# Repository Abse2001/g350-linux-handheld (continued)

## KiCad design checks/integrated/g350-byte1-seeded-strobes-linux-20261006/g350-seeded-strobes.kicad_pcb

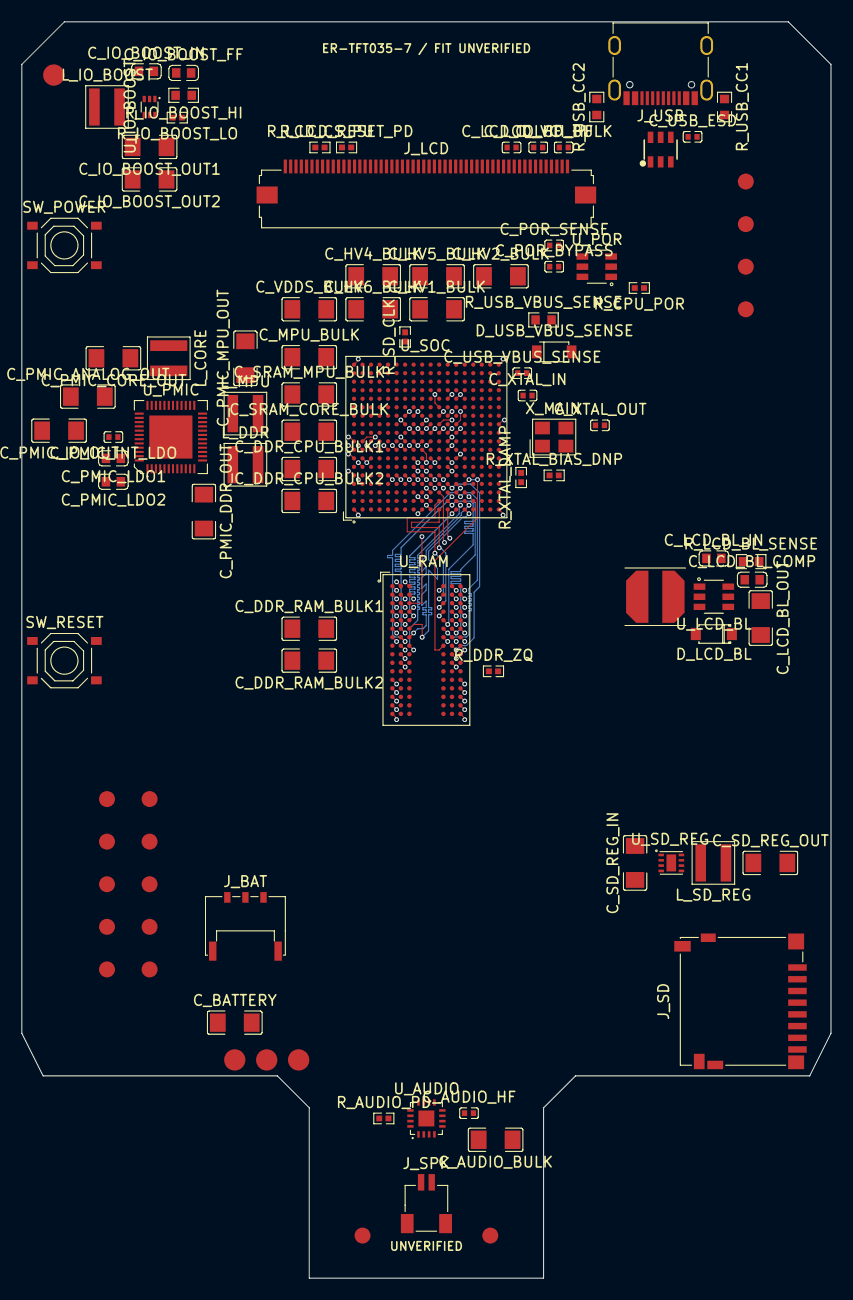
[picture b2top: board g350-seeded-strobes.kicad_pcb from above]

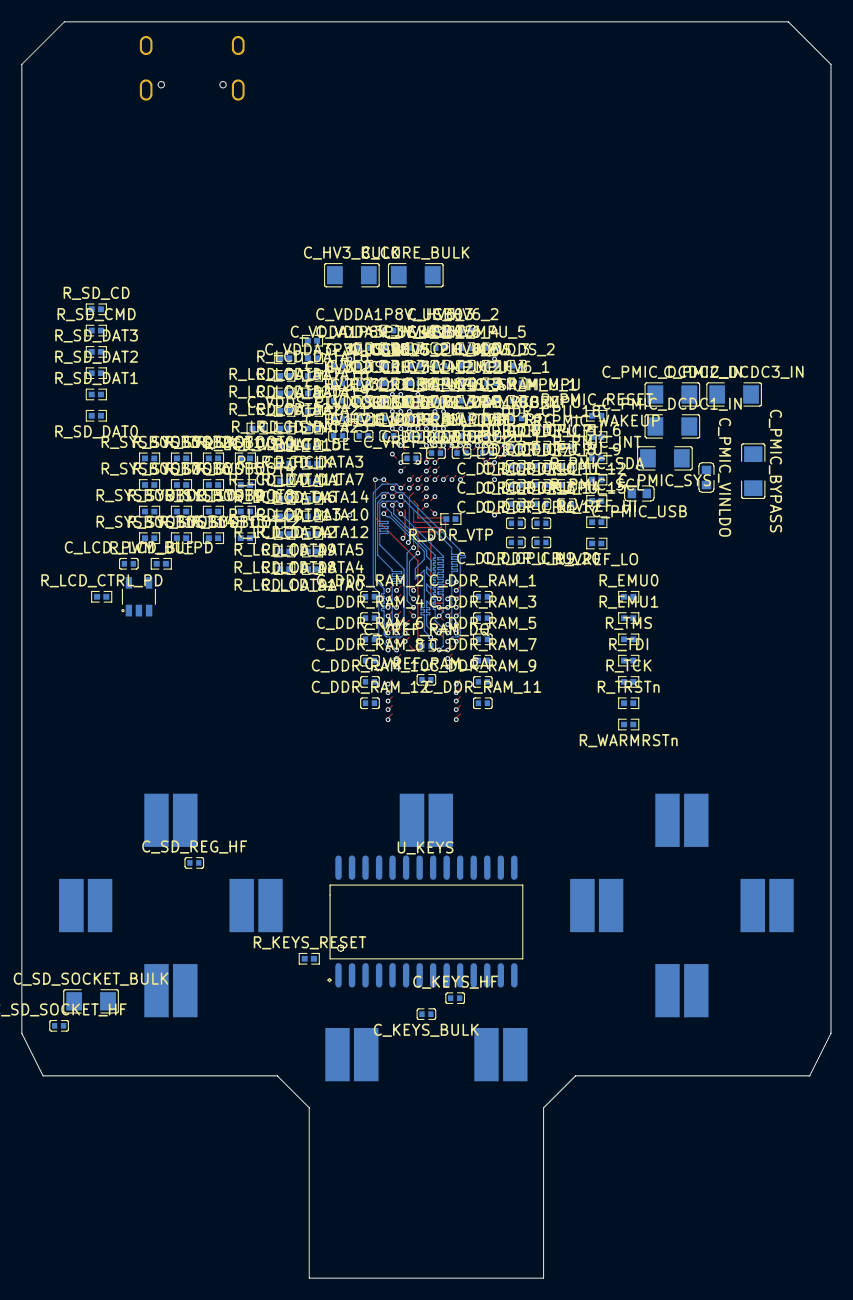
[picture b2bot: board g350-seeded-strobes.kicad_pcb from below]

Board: 4 copper layers, 76.0 x 118.0 mm, 280 parts (179 on the bottom side), 198 nets.

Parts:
C_AUDIO_BULK: 22uF; g350_C_AUDIO_BULK_392600202ec82a7f246a54de1a0c7f3d
C_AUDIO_HF: 100nF; g350_C_AUDIO_HF_6961d4c073bfaa617e1d80027784aa5d
C_BATTERY: 22uF; g350_C_BATTERY_017ffda058f040414c9f81de0dd0bc03
C_CAP_VBB_MPU: 1uF; g350_C_CAP_VBB_MPU_679ea71057047a9015a79c302bb54230
C_CAP_VDD_RTC: 1uF; g350_C_CAP_VDD_RTC_72c6b4006868de5f5e0b08be53ad331d
C_CAP_VDD_SRAM_CORE: 1uF; g350_C_CAP_VDD_SRAM_CORE_5924d8206382adc16de08362783e5903
C_CAP_VDD_SRAM_MPU: 1uF; g350_C_CAP_VDD_SRAM_MPU_53e9a9005e477ea168a55442730329e3
C_CORE_1: 10nF; g350_C_CORE_1_0342b2000da087a117fe5d42225c32e3
C_CORE_2: 10nF; g350_C_CORE_2_54f369a05f513f4169af14e2740cea83
C_CORE_3: 10nF; g350_C_CORE_3_2a942aa26bf1090252b2189e11553a3e
C_CORE_4: 10nF; g350_C_CORE_4_16e2a7a021407d412b9e52e235fc2883
C_CORE_5: 10nF; g350_C_CORE_5_6eca6c00792841a17c79e8be721c131d
C_CORE_6: 10nF; g350_C_CORE_6_27a7a2e669048146559ea05a1441c1fa
C_CORE_7: 10nF; g350_C_CORE_7_4ea172560d4493f634184a6a757528ca
C_CORE_8: 10nF; g350_C_CORE_8_1571d1400b13fb9f00b625fe09a7afa3
C_CORE_BULK: 22uF; g350_C_CORE_BULK_3f7b4a60412c6fdf3e2bd5e2427be45d
C_DDR_CPU_1: 100nF; g350_C_DDR_CPU_1_2898d3a01e3afdff13dd285e097f52bd
C_DDR_CPU_2: 100nF; g350_C_DDR_CPU_2_67dadb807238b1217c9686c2790ba39d
C_DDR_CPU_3: 100nF; g350_C_DDR_CPU_3_04949b0005c93aa1102710421a84e5e3
C_DDR_CPU_4: 100nF; g350_C_DDR_CPU_4_7030576065d281bf5b74ac1e5116d67d
C_DDR_CPU_5: 100nF; g350_C_DDR_CPU_5_695a0ce05efc373f549e619e4a408bfd
C_DDR_CPU_6: 100nF; g350_C_DDR_CPU_6_65b6c060701496017a726ba27b2fbebd
C_DDR_CPU_7: 100nF; g350_C_DDR_CPU_7_382afac04288d0614ce6a60257447ba3
C_DDR_CPU_8: 100nF; g350_C_DDR_CPU_8_4a9f542054fd29c15f5aff6269b8d503
C_DDR_CPU_9: 100nF; g350_C_DDR_CPU_9_19b02160240df7012e6bcca238c9a243
C_DDR_CPU_10: 100nF; g350_C_DDR_CPU_10_13dba440097dce9f00e007020b3ddca3
C_DDR_CPU_11: 100nF; g350_C_DDR_CPU_11_0d0559c002a7841f07b6518212142723
C_DDR_CPU_12: 100nF; g350_C_DDR_CPU_12_3df48c803396b6df2938e13e1edb0b9d
C_DDR_CPU_13: 100nF; g350_C_DDR_CPU_13_6b80522061227c7f56c4a6de4c66d13d
C_DDR_CPU_14: 100nF; g350_C_DDR_CPU_14_64aa07a05a4c31ff4fee5c5e459086bd
C_DDR_CPU_15: 100nF; g350_C_DDR_CPU_15_6a66c5a074c49b417f2270e2767fb97d
C_DDR_CPU_16: 100nF; g350_C_DDR_CPU_16_3cdb00004738d5a15196ab425bf480e3
C_DDR_CPU_17: 100nF; g350_C_DDR_CPU_17_43b14a804e0f2021586cf5c262cacb63
C_DDR_CPU_18: 100nF; g350_C_DDR_CPU_18_49dd50803f7f7adf3521a53e2ac3cf9d
C_DDR_CPU_19: 100nF; g350_C_DDR_CPU_19_7ab837607ae9f2ff708c1d5e662e47bd
C_DDR_CPU_20: 100nF; g350_C_DDR_CPU_20_7e717e207413a87f69b5d2de5f57fd3d
C_DDR_CPU_BULK1: 22uF; g350_C_DDR_CPU_BULK1_42cca9e062c3183f0852da5e521d6383
C_DDR_CPU_BULK2: 22uF; g350_C_DDR_CPU_BULK2_0096cea059d96f414bb652de0eb9eb03
C_DDR_RAM_1: 100nF; g350_C_DDR_RAM_1_6bc1b260139693616d1126de12471ee3
C_DDR_RAM_2: 100nF; g350_C_DDR_RAM_2_015ca1be6a53d08229fbbd3e41b4b502
C_DDR_RAM_3: 100nF; g350_C_DDR_RAM_3_02a1d3e07cb671e103f1485e7b66fd63
C_DDR_RAM_4: 100nF; g350_C_DDR_RAM_4_7bd1b9c2187dd3fe53329e42411cef7e
C_DDR_RAM_5: 100nF; g350_C_DDR_RAM_5_667e0aa01a29af9f652e96221b79241d
C_DDR_RAM_6: 100nF; g350_C_DDR_RAM_6_47d4d05423dba1ec7073ebd404c37994
C_DDR_RAM_7: 100nF; g350_C_DDR_RAM_7_16eadcfc7d64b0c411b43e8459fc33bc
C_DDR_RAM_8: 100nF; g350_C_DDR_RAM_8_1b022dc0256003612fbdd9023a1baea3
C_DDR_RAM_9: 100nF; g350_C_DDR_RAM_9_6be6c784003655446b7a1cfc28d570c4
C_DDR_RAM_10: 100nF; g350_C_DDR_RAM_10_4501b4c03aa3df1f3046097e25e833dd
C_DDR_RAM_11: 100nF; g350_C_DDR_RAM_11_114793fc7cf8063c175787845458eabc
C_DDR_RAM_12: 100nF; g350_C_DDR_RAM_12_5afa68c065583e616fb614027a13e9a3
C_DDR_RAM_BULK1: 22uF; g350_C_DDR_RAM_BULK1_7a3cf3001fccb51f3aa388c26aec395d
C_DDR_RAM_BULK2: 22uF; g350_C_DDR_RAM_BULK2_4ed11af05b399cd067a21eb0740aa090
C_HV1_1: 10nF; g350_C_HV1_1_1bbd9d40115fc79f0701f1fe035be3a3
C_HV1_2: 10nF; g350_C_HV1_2_589531604e375bbf43d9861e397bb07d
C_HV1_BULK: 22uF; g350_C_HV1_BULK_0e160b20688649013d09791e1d66c4c3
C_HV2_1: 10nF; g350_C_HV2_1_286e92001e10bc5f13b2e6be0955111d
C_HV2_2: 10nF; g350_C_HV2_2_44f53bc03a97661f3039907e25dbbadd
C_HV2_BULK: 22uF; g350_C_HV2_BULK_36e7d60049bfe43f359861824b0f58bd
C_HV3_1: 10nF; g350_C_HV3_1_4a54676054b23d015f1012a2696de843
C_HV3_2: 10nF; g350_C_HV3_2_0600219e475cfffe774621a235e94342
C_HV3_BULK: 22uF; g350_C_HV3_BULK_01978c807dc0b94102e700fe7c7144c3
C_HV4_1: 10nF; g350_C_HV4_1_5f4d47201df068c0236c75a064c95400
C_HV4_2: 10nF; g350_C_HV4_2_52375f805c95352166f30ac27150e063
C_HV4_BULK: 22uF; g350_C_HV4_BULK_4c8c50e84023cf0833bb4d282752cb48
C_HV5_1: 10nF; g350_C_HV5_1_2c2b7cc41531619c568e3ffc6814e1a4
C_HV5_2: 10nF; g350_C_HV5_2_151adae00abd053f005f2f9e09fea603
C_HV5_BULK: 22uF; g350_C_HV5_BULK_328c21004ccc24c133db957e4b7cb043
C_HV6_1: 10nF; g350_C_HV6_1_5a03dea04fa608ff4548335e3aea5dbd
C_HV6_2: 10nF; g350_C_HV6_2_19f106a62659888632c20a663f2a8c46
C_HV6_3: 10nF; g350_C_HV6_3_359744a4292ec2c41cc640e4105dbf04
C_HV6_4: 10nF; g350_C_HV6_4_03d77e600686574110e42ce21b420283
C_HV6_5: 10nF; g350_C_HV6_5_7a2ab6807b7773df71199e3e66bbc89d
C_HV6_6: 10nF; g350_C_HV6_6_67bea9822c90e43e3f1f8e02552fffbe
C_HV6_BULK: 22uF; g350_C_HV6_BULK_46306140223f9cc0755065400ce06740
C_IO_BOOST_FF: 220pF; g350_C_IO_BOOST_FF_302f3d726420504e079021f273409432
C_IO_BOOST_IN: 4.7uF; g350_C_IO_BOOST_IN_08beb780019f1e210bfcf3c2165ac963
C_IO_BOOST_OUT1: 22uF; g350_C_IO_BOOST_OUT1_14e02c206a7819a1162fa09e6928a523
C_IO_BOOST_OUT2: 22uF; g350_C_IO_BOOST_OUT2_6408e06257a05e824b37dca23ecf5ac2
C_KEYS_BULK: 1uF; g350_C_KEYS_BULK_1be086401182b09f0724dafe0338faa3
C_KEYS_HF: 100nF; g350_C_KEYS_HF_44d2b8440375d9e43de7047c7f43e2dc
C_LCD_BL_COMP: 220nF; g350_C_LCD_BL_COMP_525d3b606c45e6402ae907e01673d680
C_LCD_BL_IN: 4.7uF; g350_C_LCD_BL_IN_0b6432627714a4a21d3ae91e4e758922
C_LCD_BL_OUT: 4.7uF; g350_C_LCD_BL_OUT_0caa00e25f06715e35491c62366755de
C_LCD_BULK: 1uF; g350_C_LCD_BULK_57e6e716168a08b62ad2d5aa6c2fb40a
C_LCD_IO_HF: 100nF; g350_C_LCD_IO_HF_7c8ea15e17c0ec6253ef85de406007e2
C_LCD_PWM_BUF: 100nF; g350_C_LCD_PWM_BUF_259675e00fd5636105ebaf1e1bacc19d
C_LCD_VCI_HF: 100nF; g350_C_LCD_VCI_HF_09551ea43807bfbc79649e1c453e8384
C_MPU_1: 10nF; g350_C_MPU_1_3440648029e28edf1f84b93e1526e39d
C_MPU_2: 10nF; g350_C_MPU_2_55bfbe004b61e85f410412be36a63d1d
C_MPU_3: 10nF; g350_C_MPU_3_4aaa614a210610f673497cca07990a8a
C_MPU_4: 10nF; g350_C_MPU_4_30f36240635c2b80085446c07404b900
C_MPU_5: 10nF; g350_C_MPU_5_50489dc045eac81f3b8cf27e312f1cdd
C_MPU_BULK: 22uF; g350_C_MPU_BULK_60aa59c45441d7e447d956043b70d424
C_PMIC_ANALOG_OUT: 22uF; g350_C_PMIC_ANALOG_OUT_46d14e4c4d7e3f741e3232cc761d5af4
C_PMIC_BYPASS: 22uF; g350_C_PMIC_BYPASS_021084146dc0f654268e976c4521dad4
C_PMIC_CORE_OUT: 22uF; g350_C_PMIC_CORE_OUT_037bdbee6f2c4e2e25233f92468d32ae
C_PMIC_DCDC1_IN: 22uF; g350_C_PMIC_DCDC1_IN_007686b40cdf089419478a7425b00c54
C_PMIC_DCDC2_IN: 22uF; g350_C_PMIC_DCDC2_IN_4572253051daa7105e4328f06aabaad0
C_PMIC_DCDC3_IN: 22uF; g350_C_PMIC_DCDC3_IN_07be747404aa0d6c11128f4c1d7b112c
C_PMIC_DDR_OUT: 22uF; g350_C_PMIC_DDR_OUT_1375ad7e1fde2f5e2c46b13e38af331e
C_PMIC_INT_LDO: 100nF; g350_C_PMIC_INT_LDO_5ff8ced853904cf84727cb183abf4938
C_PMIC_IO_OUT: 22uF; g350_C_PMIC_IO_OUT_1f3a76c0751517000964a4c0624bcd80
C_PMIC_LDO1: 2.2uF; g350_C_PMIC_LDO1_7d4e3bc270e5b9e2647d38025814b622
C_PMIC_LDO2: 2.2uF; g350_C_PMIC_LDO2_4357e14a50f7ac761ab8c5ca7996c7f6
C_PMIC_MPU_OUT: 22uF; g350_C_PMIC_MPU_OUT_740397dc7f93e644732b646466c2e284
C_PMIC_SYS: 22uF; g350_C_PMIC_SYS_601c39a66c84bb8678ed3d667aaa40ba
C_PMIC_USB: 4.7uF; g350_C_PMIC_USB_0efb8f9c1b64117c27cc935c3435153c
C_PMIC_VINLDO: 4.7uF; g350_C_PMIC_VINLDO_102a47fa7bdaba3a1874d386533b9eba
C_POR_BYPASS: 100nF; g350_C_POR_BYPASS_563d331649d4b1363d6c2f563103ad76
C_POR_SENSE: 10nF; g350_C_POR_SENSE_4b57af6457c031446428b32470913504
C_SD_REG_HF: 100nF; g350_C_SD_REG_HF_5ceb2860528d52bf482f7d1e3dd1a77d
C_SD_REG_IN: 22uF; g350_C_SD_REG_IN_3b687020310a9a7f26acc4de1c4eef3d
C_SD_REG_OUT: 22uF; g350_C_SD_REG_OUT_00ae91e009af43c1140d19621e6aef03
C_SD_SOCKET_BULK: 22uF; g350_C_SD_SOCKET_BULK_2d0df660376bcc0141c9a1a24c277743
C_SD_SOCKET_HF: 100nF; g350_C_SD_SOCKET_HF_0600e8400fc02a3f25813cbe3b424f3d
C_SRAM_CORE_1: 10nF; g350_C_SRAM_CORE_1_17c23b1253ee372e406156922b4f1bae
C_SRAM_CORE_BULK: 22uF; g350_C_SRAM_CORE_BULK_59a8414a6610c32a7279450a7ee1c6ea
C_SRAM_MPU_1: 10nF; g350_C_SRAM_MPU_1_2d4a523067053b9004ab36b0705ba8f0
C_SRAM_MPU_BULK: 22uF; g350_C_SRAM_MPU_BULK_34400efa634ff30605200afa6d9008fa
C_USB_ESD: 100nF; g350_C_USB_ESD_4c3c73561f73feea74db8ed6092b1c96
C_USB_VBUS_SENSE: 100nF; g350_C_USB_VBUS_SENSE_0ab2960a171b17ea238399ca2fec1baa
C_VDDA1P8V_USB0: 10nF; g350_C_VDDA1P8V_USB0_049716a07c10a39f0347a2227d60181d
C_VDDA1P8V_USB1: 10nF; g350_C_VDDA1P8V_USB1_21ec52341f708c2c60cd6a8c5dd5b714
C_VDDA3P3V_USB0: 10nF; g350_C_VDDA3P3V_USB0_3a28c3e207341a7e4890f8de761228c2
C_VDDA3P3V_USB1: 10nF; g350_C_VDDA3P3V_USB1_0e5160a018af3641230d0be22d6ae183
C_VDDS_1: 10nF; g350_C_VDDS_1_7de2d39e3c85f53e04d6e9224633c782
C_VDDS_2: 10nF; g350_C_VDDS_2_017dd3c86d2e4608272147b8448f2a88
C_VDDS_3: 10nF; g350_C_VDDS_3_7d1b97521733f66e547c7bd23fd311ee
C_VDDS_4: 10nF; g350_C_VDDS_4_624946806ca71c217704f1c27e9d389d
C_VDDS_BULK: 22uF; g350_C_VDDS_BULK_2d863c886a09c5780199c77866d63688
C_VDDS_OSC: 10nF; g350_C_VDDS_OSC_010a849c426762fc7c3bbea43adee044
C_VDDS_PLL_CORE_LCD: 10nF; g350_C_VDDS_PLL_CORE_LCD_0cf9245c3463ba0475c0986448e2893c
C_VDDS_PLL_DDR: 10nF; g350_C_VDDS_PLL_DDR_2cbf10383ef16208555e2bb816524688
C_VDDS_PLL_MPU: 10nF; g350_C_VDDS_PLL_MPU_1fe6c4264bc9ae1a4885dfa6232a929a
C_VDDS_RTC: 10nF; g350_C_VDDS_RTC_4b81d3604123fdbf36c6281e2c68527d
C_VREF_CPU: 100nF; g350_C_VREF_CPU_549572043fba1bbc2bf656846859373c
C_VREF_RAM_CA: 100nF; g350_C_VREF_RAM_CA_3bcad500316cff5f270f29be1cb1541d
C_VREF_RAM_DQ: 100nF; g350_C_VREF_RAM_DQ_70ab39c823a453f8480c1e484c436f78
C_XTAL_IN: 18pF; g350_C_XTAL_IN_7a27b68438cad8240892063c49eee49c
C_XTAL_OUT: 18pF; g350_C_XTAL_OUT_0ec3049e501fe2fe6e833ea22d266042
D_LCD_BL: D; g350_D_LCD_BL_150c64e47f4328dc1392b69c581dbba4
D_USB_VBUS_SENSE: D; g350_D_USB_VBUS_SENSE_33eeefac27866dcc1b1debec0eb56a0c
J_BAT: DF65-3P-1.7V(21); g350_J_BAT_399be774556bf9ec1b8c24b4737bbcac
J_LCD: 0.5-54PFGPZ; g350_J_LCD_3b2712de2ebe90fe22560f1e15ed8d3e
J_SD: DM3D-SF; g350_J_SD_4162de604bc0b401561e89a2607c5f43
J_SPK: SM02B-SRSS-TB(LF)(SN); g350_J_SPK_06bad6e0789d6ee1080a4b5e774dfa63
J_USB: TYPE-C-31-M-12; g350_J_USB_48664640098e047f5b824f3e52896603
KEY_A: g350_KEY_A_37e0d400477771c13930487e4627fd43
KEY_B: g350_KEY_B_25c1e3a05ae5d69f24726f225c354b1d
KEY_DOWN: g350_KEY_DOWN_4cb4b49c404c32bc33e3b0dc277b2efc
KEY_LEFT: g350_KEY_LEFT_4ab0b7923e4835b231dfb3d2257731f2
KEY_MENU: g350_KEY_MENU_417a98403f2d21ff402b23c2407c967d
KEY_RIGHT: g350_KEY_RIGHT_4e00fda041987bc0352ff9e028c77800
KEY_SELECT: g350_KEY_SELECT_61751792550c95b248a413d23c3b91f2
KEY_START: g350_KEY_START_26a91e0059fe9c3f2559a9825b4e10bd
KEY_UP: g350_KEY_UP_0916888e0351f9520fba7b321c22fd12
KEY_X: g350_KEY_X_24e3d1005bc3e93f23945c825d135dbd
KEY_Y: g350_KEY_Y_7d79776001dece617ec8ebde008f59e3
L_CORE: 2.2µH; g350_L_CORE_6e3a994c2614f474459b7dcc4eb40ff4
L_DDR: 2.2µH; g350_L_DDR_37d9e0a022965d417d069b22288926fd
L_IO_BOOST: 2.2µH; g350_L_IO_BOOST_19dc99d87db3682815436a28532c93d8
L_LCD_BL: 10µH; g350_L_LCD_BL_7a05cdf81a49bfc85166b27842e8db48
L_MPU: 2.2µH; g350_L_MPU_2832a2661bca20860f619ea602f91cc6
L_SD_REG: 2.2µH; g350_L_SD_REG_6f8917204f1a0a800dbd2c20339fb240
R_AUDIO_PD: 100kΩ; g350_R_AUDIO_PD_705229de63e9a7fe5781261e4b18a43e
R_CPU_POR: 100kΩ; g350_R_CPU_POR_0e96d7361aff59162767daf633d05cd6
R_DDR_VTP: 49.9Ω; g350_R_DDR_VTP_62afb6fc0900bb4474b12d841f9e603c
R_DDR_ZQ: 240Ω; g350_R_DDR_ZQ_48b7fad64b9792ea2018df567436ae6a
R_EMU0: 4.7kΩ; g350_R_EMU0_2cf14140789e80df1e2e42fe3c41fae3
R_EMU1: 4.7kΩ; g350_R_EMU1_26ad8ce07ee2353f2471f75e35fe4683
R_IO_BOOST_HI: 732kΩ; g350_R_IO_BOOST_HI_60bcda100af3983076a40a701dab8350
R_IO_BOOST_LO: 100kΩ; g350_R_IO_BOOST_LO_4b45fc2657ae7e066416ffe6707f81c6
R_KEYS_RESET: 10kΩ; g350_R_KEYS_RESET_7fef33c00096edff7ec157c201e6627d
R_LCD_BL_PD: 33kΩ; g350_R_LCD_BL_PD_3da5ed1203b6f14e4513cfae798f51f2
R_LCD_BL_SENSE: 15Ω; g350_R_LCD_BL_SENSE_241f56621d3d87fe5e9a665e6008bb42
R_LCD_CS_PU: 100kΩ; g350_R_LCD_CS_PU_42fc95203c5bb0a1444c099e3b0c3c23
R_LCD_CTRL_PD: 33kΩ; g350_R_LCD_CTRL_PD_4f27a60c1c88cc3477c6c18c0c164f4c
R_LCD_DATA0: 33Ω; g350_R_LCD_DATA0_035b4cb444b82b1479eaf68c388e182c
R_LCD_DATA1: 33Ω; g350_R_LCD_DATA1_4785264c062847ec3b3496747c9174d4
R_LCD_DATA2: 33Ω; g350_R_LCD_DATA2_29a0434013df30c101e1e1be17a2f43d
R_LCD_DATA3: 33Ω; g350_R_LCD_DATA3_2fb8c5204579d79f5b3aea1e70fbfc9d
R_LCD_DATA4: 33Ω; g350_R_LCD_DATA4_7d91444067d031c1520f1f423c4e0cc3
R_LCD_DATA5: 33Ω; g350_R_LCD_DATA5_5165e4cc1009066c3153d7f472b0b654
R_LCD_DATA6: 33Ω; g350_R_LCD_DATA6_45ac47e05b6d5a5f712e6cde791080a3
R_LCD_DATA7: 33Ω; g350_R_LCD_DATA7_043c42d83d209b887e7d79e84025a7b8
R_LCD_DATA8: 33Ω; g350_R_LCD_DATA8_07e87f400dd8933f2399a5be395ab83d
R_LCD_DATA9: 33Ω; g350_R_LCD_DATA9_032a9464448772c47a1baedc38bed07c
R_LCD_DATA10: 33Ω; g350_R_LCD_DATA10_0ece68a2502b47026e77da9e2d1afc3e
R_LCD_DATA11: 33Ω; g350_R_LCD_DATA11_3b2e9852062e460e478b246e7717fd32
R_LCD_DATA12: 33Ω; g350_R_LCD_DATA12_6b3dd740557cc4c13fbbb24229fa9fc3
R_LCD_DATA13: 33Ω; g350_R_LCD_DATA13_2ec8a15a12943d0653f11b666ab2063a
R_LCD_DATA14: 33Ω; g350_R_LCD_DATA14_77d33fc0726badc15caa9b4246e988c3
R_LCD_DATA15: 33Ω; g350_R_LCD_DATA15_696b81ac55379ff413dac1942d821ccc
R_LCD_DATA16: 33Ω; g350_R_LCD_DATA16_017596a042d275007bd0aca03a73ce40
R_LCD_DATA17: 33Ω; g350_R_LCD_DATA17_496adc60080dfe00394ee0607aabbec0
R_LCD_DATA18: 33Ω; g350_R_LCD_DATA18_49c541405f8653bf7547663e74f78743
R_LCD_DATA19: 33Ω; g350_R_LCD_DATA19_22c740c03888533f4e4965be640a783d
R_LCD_DATA20: 33Ω; g350_R_LCD_DATA20_10270f40059a033f1b5b15be311c283d
R_LCD_DATA21: 33Ω; g350_R_LCD_DATA21_21c9ab1e6326897e5b7c98221a1fb9c2
R_LCD_DATA22: 33Ω; g350_R_LCD_DATA22_2916c7e21846167e59a2f4de65002cc2
R_LCD_DATA23: 33Ω; g350_R_LCD_DATA23_162411000062fe81155e13fe2b1f267d
R_LCD_DE: 33Ω; g350_R_LCD_DE_21aebc9a630b9afa5b9786a61a3aa846
R_LCD_HSYNC: 33Ω; g350_R_LCD_HSYNC_4912610033514e811d903c0207cf2983
R_LCD_PCLK: 33Ω; g350_R_LCD_PCLK_6736df807cf7f1ff6d46fb825785e903
R_LCD_RESET_PD: 100kΩ; g350_R_LCD_RESET_PD_2dba672038183cc1427612624cd3e803
R_LCD_VSYNC: 33Ω; g350_R_LCD_VSYNC_58e45c7a65bec5262461e6c61cfaf79a
R_PMIC_INT: 10kΩ; g350_R_PMIC_INT_0a53a33e5e1c5ac23973a73e2efc56c2
R_PMIC_RESET: 100kΩ; g350_R_PMIC_RESET_50336474183c998c7f53687416e36a74
R_PMIC_SCL: 4.7kΩ; g350_R_PMIC_SCL_17264e325149afce464652322229abce
R_PMIC_SDA: 4.7kΩ; g350_R_PMIC_SDA_10bcf8b857b305483fdcfcb828930148
R_PMIC_WAKEUP: 100kΩ; g350_R_PMIC_WAKEUP_03ea4dc46485b03c330a51c43565ac3c
R_SD_CD: 10kΩ; g350_R_SD_CD_782b85267b6bf8fa6f03771a629af53a
R_SD_CLK: 33Ω; g350_R_SD_CLK_6b5b0ea0154cab9f6a0b9a22169c201d
R_SD_CMD: 10kΩ; g350_R_SD_CMD_41a93f283540bd4828d83b681c6fb988
R_SD_DAT0: 10kΩ; g350_R_SD_DAT0_380336f0446bb8d050d43ab05d3cbc90
R_SD_DAT1: 10kΩ; g350_R_SD_DAT1_2667e69619ff64b60d96e2d6012e60f6
R_SD_DAT2: 10kΩ; g350_R_SD_DAT2_7b2cfbe4786a823c6c02005c5f997e7c
R_SD_DAT3: 10kΩ; g350_R_SD_DAT3_1cc1de5e292a603e3592e21e41fb63fe
R_SYSBOOT0: 10kΩ; g350_R_SYSBOOT0_77f1a8847ba5d59c6f3d53bc62d4d1dc
R_SYSBOOT1: 10kΩ; g350_R_SYSBOOT1_0701a252136a24321fd2a6122c3b27f2
R_SYSBOOT2: 10kΩ; g350_R_SYSBOOT2_65bec8b6595646d64cedc4f640854316
R_SYSBOOT3: 10kΩ; g350_R_SYSBOOT3_4e46d6185aaf57f86717d9d873805bb8
R_SYSBOOT4: 10kΩ; g350_R_SYSBOOT4_6439765c301617643b9a5adc58b532e4
R_SYSBOOT5: 10kΩ; g350_R_SYSBOOT5_23f8d23247b7a00e4c97edb21f18848e
R_SYSBOOT6: 10kΩ; g350_R_SYSBOOT6_12f805d67ea8781615a715aa56095c96
R_SYSBOOT7: 10kΩ; g350_R_SYSBOOT7_49e8ddde4a66afe22149c25e7305cb62
R_SYSBOOT8: 10kΩ; g350_R_SYSBOOT8_15268114218f02f42df784d43a6006b4
R_SYSBOOT9: 10kΩ; g350_R_SYSBOOT9_5bc9851e4f61033e42f8815e368fff7e
R_SYSBOOT10: 10kΩ; g350_R_SYSBOOT10_37760fda43de91ba5047139a5caf957a
R_SYSBOOT11: 10kΩ; g350_R_SYSBOOT11_354a5b2e28e1d94e1c79576e1010d58e
R_SYSBOOT12: 10kΩ; g350_R_SYSBOOT12_092c996274dd0ba21f72821e4c3df022
R_SYSBOOT13: 10kΩ; g350_R_SYSBOOT13_40256b3e542a228217864fbe7cc93e02
R_SYSBOOT14: 10kΩ; g350_R_SYSBOOT14_771643461d394a7a4e7727c645d865fa
R_SYSBOOT15: 10kΩ; g350_R_SYSBOOT15_51f8e4b219b78d8e7a9800320ee78df2
R_TCK: 4.7kΩ; g350_R_TCK_2eaaa4542242227415d9a09409711eb4
R_TDI: 4.7kΩ; g350_R_TDI_6ba285d65f3a03f652d1821646690036
R_TMS: 4.7kΩ; g350_R_TMS_2069d8807ada16612ab5abbe2fba9223
R_TRSTn: 4.7kΩ; g350_R_TRSTn_0e4d3d2e1ab5bf0e271e40ee3386c2ce
R_USB_CC1: 5.1kΩ; g350_R_USB_CC1_6c2a3bec5fc1ba0c5359382c46f0b64c
R_USB_CC2: 5.1kΩ; g350_R_USB_CC2_7766f5547c3088cc6fc806ec635f850c
R_USB_VBUS_SENSE: 1.2kΩ; g350_R_USB_VBUS_SENSE_38e6c8ac2c7e46cc2015c4ec13ad430c
R_VREF_HI: 10kΩ; g350_R_VREF_HI_49987f021ed77efe78b8830210488502
R_VREF_LO: 10kΩ; g350_R_VREF_LO_02b097ae6b2095ae2c6f6c523c0091ae
R_WARMRSTn: 4.7kΩ; g350_R_WARMRSTn_4b451eb057ada09064162270707ea450
R_XTAL_BIAS_DNP: 1MΩ; g350_R_XTAL_BIAS_DNP_4830bf5a4c1ece661f91a3da74bde9e6
R_XTAL_DAMP: 0Ω; g350_R_XTAL_DAMP_59294d0817cc6ea829906fb86aed4e18
SW_POWER: SW_POWER; g350_SW_POWER_6cca27007dce1aff68665cfe52fe9efd
SW_RESET: SW_RESET; g350_SW_RESET_1b7dd7800f1555a002acd3c009bbae20
TP_BAT_GND: TP_BAT_GND; g350_TP_BAT_GND_6eabc8867b144a66788333ba6c1ab1da
TP_BAT_INPUT: TP_BAT_INPUT; g350_TP_BAT_INPUT_7719adfe7c7dd02270154e4263accc62
TP_BAT_NTC: TP_BAT_NTC; g350_TP_BAT_NTC_72e2bb427f4b3d22744c40fe67e3bf1e
TP_GND: TP_GND; g350_TP_GND_7357bb6c7fc03d4c73d740d4676ebef4
TP_IO_3V3: TP_IO_3V3; g350_TP_IO_3V3_06da58721342da521fab5c322c13de12
TP_JTAG_EMU0: TP_JTAG_EMU0; g350_TP_JTAG_EMU0_0fb1768c0348f4ac091f8d3415880f14
TP_JTAG_EMU1: TP_JTAG_EMU1; g350_TP_JTAG_EMU1_302df6783c96785848fefa3855677c18
TP_JTAG_TCK: TP_JTAG_TCK; g350_TP_JTAG_TCK_52db3b804672b9a03a0a37c02da1b5e0
TP_JTAG_TDI: TP_JTAG_TDI; g350_TP_JTAG_TDI_263d458a19d4c3aa0d6c41ca0103bfea
TP_JTAG_TDO: TP_JTAG_TDO; g350_TP_JTAG_TDO_19a2277a260aa95a32732b3a3edbad1a
TP_JTAG_TMS: TP_JTAG_TMS; g350_TP_JTAG_TMS_46401d7052a89f505f1121306b79a310
TP_JTAG_TRSTn: TP_JTAG_TRSTn; g350_TP_JTAG_TRSTn_5ccbec6e69346e4e759cf02e7dfa8df2
TP_SPK_N: TP_SPK_N; g350_TP_SPK_N_29eb7dc056bc3c7f289c0942580bb0fd
TP_SPK_P: TP_SPK_P; g350_TP_SPK_P_4740e0ae53a9628e6011e46e6c7a664e
TP_UART_GND: TP_UART_GND; g350_TP_UART_GND_4374da44370c58642aa3d6841e3b54a4
TP_UART_IO_3V3: TP_UART_IO_3V3; g350_TP_UART_IO_3V3_37926c4c2b29ea6c1ec1688c1258e6ac
TP_UART_UART0_RX: TP_UART_UART0_RX; g350_TP_UART_UART0_RX_6f91774e6328f56e56c0738e4a57f1ae
TP_UART_UART0_TX: TP_UART_UART0_TX; g350_TP_UART_UART0_TX_6451eba870ba6d887d22ef6876748eb8
TP_USB_INPUT: TP_USB_INPUT; g350_TP_USB_INPUT_44caabc05a3269c16f9a27c27afe1a3d
TP_WARM_RESETn: TP_WARM_RESETn; g350_TP_WARM_RESETn_3c4f6c822fe6eaa2237e68c21715e6e2
U_AUDIO: MAX98357AETE+T; g350_U_AUDIO_682f4a401728fb81697ebebe15d98703
U_IO_BOOST: TPS61023DRLR; g350_U_IO_BOOST_725420a07844215f62dc635e4d74a55d
U_KEYS: MCP23017-E/SO; g350_U_KEYS_61b84c806c1622217673f7c27f2e329d
U_LCD_BL: TPS61165DBVR; g350_U_LCD_BL_6bf43af45f8bb9145323373446bab554
U_LCD_PWM_BUF: SN74LVC1G125DBVR; g350_U_LCD_PWM_BUF_0d91a2ce19fa24ae2662a68e32cb286e
U_PMIC: TPS65217CRSLR; g350_U_PMIC_03b5ea0011b1d401271992023c815003
U_POR: TPS3808G33DBVR; g350_U_POR_50824ce65ceacec6695350a675bbd286
U_RAM: MT41K256M16TW-107:P; g350_U_RAM_555ec8005030fa1f0a3f43c264af81a3
U_SD_REG: TPS62162DSGR; g350_U_SD_REG_112fd9806f77e0bf0fe0650270c7553d
U_SOC: AM3352BZCZ100; g350_U_SOC_333c072c3533f6d4625c0b2c0613f2d4
U_USB_ESD: USBLC6-2SC6; g350_U_USB_ESD_77106bb215a86fb24bbf8c4e52d877b2
X_MAIN: X_MAIN; g350_X_MAIN_68bf15ec5c56940c4fee122c4385904c

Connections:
ANALOG_1V8: C_HV1_1.1, C_HV1_2.1, C_HV1_BULK.1, C_HV3_1.1, C_HV3_2.1, C_HV3_BULK.1, C_LCD_PWM_BUF.1, C_PMIC_ANALOG_OUT.1, C_SRAM_CORE_1.1, C_SRAM_CORE_BULK.1, C_SRAM_MPU_1.1, C_SRAM_MPU_BULK.1, C_VDDA1P8V_USB0.1, C_VDDA1P8V_USB1.1, C_VDDS_OSC.1, C_VDDS_PLL_CORE_LCD.1, C_VDDS_PLL_DDR.1, C_VDDS_PLL_MPU.1, U_LCD_PWM_BUF.5, U_PMIC.40, U_SOC.113, U_SOC.122, U_SOC.140, U_SOC.149, U_SOC.166, U_SOC.177, U_SOC.195, U_SOC.212, U_SOC.230, U_SOC.260, U_SOC.283, U_SOC.285
AUDIO_BCLK: U_AUDIO.16, U_SOC.217
AUDIO_DIN: U_AUDIO.1, U_SOC.202
AUDIO_ENABLE: R_AUDIO_PD.1, U_AUDIO.4, U_SOC.235
AUDIO_LRCLK: U_AUDIO.14, U_SOC.218
BAT_NTC: J_BAT.2, TP_BAT_NTC.1, U_PMIC.11
CAP_VBB_MPU: C_CAP_VBB_MPU.1, U_SOC.165
CAP_VDD_RTC: C_CAP_VDD_RTC.1, U_SOC.94
CAP_VDD_SRAM_CORE: C_CAP_VDD_SRAM_CORE.1, U_SOC.148
CAP_VDD_SRAM_MPU: C_CAP_VDD_SRAM_MPU.1, U_SOC.184
CPU_PORn: R_CPU_POR.2, U_POR.1, U_SOC.254
DDR_1V5: C_DDR_CPU_1.1, C_DDR_CPU_2.1, C_DDR_CPU_3.1, C_DDR_CPU_4.1, C_DDR_CPU_5.1, C_DDR_CPU_6.1, C_DDR_CPU_7.1, C_DDR_CPU_8.1, C_DDR_CPU_9.1, C_DDR_CPU_10.1, C_DDR_CPU_11.1, C_DDR_CPU_12.1, C_DDR_CPU_13.1, C_DDR_CPU_14.1, C_DDR_CPU_15.1, C_DDR_CPU_16.1, C_DDR_CPU_17.1, C_DDR_CPU_18.1, C_DDR_CPU_19.1, C_DDR_CPU_20.1, C_DDR_CPU_BULK1.1, C_DDR_CPU_BULK2.1, C_DDR_RAM_1.1, C_DDR_RAM_2.1, C_DDR_RAM_3.1, C_DDR_RAM_4.1, C_DDR_RAM_5.1, C_DDR_RAM_6.1, C_DDR_RAM_7.1, C_DDR_RAM_8.1, C_DDR_RAM_9.1, C_DDR_RAM_10.1, C_DDR_RAM_11.1, C_DDR_RAM_12.1, C_DDR_RAM_BULK1.1, C_DDR_RAM_BULK2.1, C_PMIC_DDR_OUT.1, L_DDR.2, R_VREF_HI.1, U_PMIC.19, U_RAM.1, U_RAM.3, U_RAM.6, U_RAM.13, U_RAM.15, U_RAM.18, U_RAM.20, U_RAM.24, U_RAM.26, U_RAM.55, U_RAM.65, U_RAM.74, U_RAM.83, U_RAM.84, U_RAM.85, U_RAM.88, U_RAM.93, U_RAM.95, U_SOC.77, U_SOC.78, U_SOC.79, U_SOC.80, U_SOC.81, U_SOC.82, U_SOC.83
DDR_VREF: C_VREF_CPU.1, C_VREF_RAM_CA.1, C_VREF_RAM_DQ.1, R_VREF_HI.2, R_VREF_LO.1, U_RAM.8, U_RAM.76, U_SOC.63
DDR_VTP: R_DDR_VTP.1, U_SOC.45
DDR_ZQ: R_DDR_ZQ.1, U_RAM.75
GND: C_AUDIO_BULK.2, C_AUDIO_HF.2, C_BATTERY.2, C_CAP_VBB_MPU.2, C_CAP_VDD_RTC.2, C_CAP_VDD_SRAM_CORE.2, C_CAP_VDD_SRAM_MPU.2, C_CORE_1.2, C_CORE_2.2, C_CORE_3.2, C_CORE_4.2, C_CORE_5.2, C_CORE_6.2, C_CORE_7.2, C_CORE_8.2, C_CORE_BULK.2, C_DDR_CPU_1.2, C_DDR_CPU_2.2, C_DDR_CPU_3.2, C_DDR_CPU_4.2, C_DDR_CPU_5.2, C_DDR_CPU_6.2, C_DDR_CPU_7.2, C_DDR_CPU_8.2, C_DDR_CPU_9.2, C_DDR_CPU_10.2, C_DDR_CPU_11.2, C_DDR_CPU_12.2, C_DDR_CPU_13.2, C_DDR_CPU_14.2, C_DDR_CPU_15.2, C_DDR_CPU_16.2, C_DDR_CPU_17.2, C_DDR_CPU_18.2, C_DDR_CPU_19.2, C_DDR_CPU_20.2, C_DDR_CPU_BULK1.2, C_DDR_CPU_BULK2.2, C_DDR_RAM_1.2, C_DDR_RAM_2.2, C_DDR_RAM_3.2, C_DDR_RAM_4.2, C_DDR_RAM_5.2, C_DDR_RAM_6.2, C_DDR_RAM_7.2, C_DDR_RAM_8.2, C_DDR_RAM_9.2, C_DDR_RAM_10.2, C_DDR_RAM_11.2, C_DDR_RAM_12.2, C_DDR_RAM_BULK1.2, C_DDR_RAM_BULK2.2, C_HV1_1.2, C_HV1_2.2, C_HV1_BULK.2, C_HV2_1.2, C_HV2_2.2, C_HV2_BULK.2, C_HV3_1.2, C_HV3_2.2, C_HV3_BULK.2, C_HV4_1.2, C_HV4_2.2, C_HV4_BULK.2, C_HV5_1.2, C_HV5_2.2, C_HV5_BULK.2, C_HV6_1.2, C_HV6_2.2, C_HV6_3.2, C_HV6_4.2, C_HV6_5.2, C_HV6_6.2, C_HV6_BULK.2, C_IO_BOOST_IN.2, C_IO_BOOST_OUT1.2, C_IO_BOOST_OUT2.2, C_KEYS_BULK.2, C_KEYS_HF.2, C_LCD_BL_COMP.2, C_LCD_BL_IN.2, C_LCD_BL_OUT.2, C_LCD_BULK.2, C_LCD_IO_HF.2, C_LCD_PWM_BUF.2, C_LCD_VCI_HF.2, C_MPU_1.2, C_MPU_2.2, C_MPU_3.2, C_MPU_4.2, C_MPU_5.2, C_MPU_BULK.2, C_PMIC_ANALOG_OUT.2, C_PMIC_BYPASS.2, C_PMIC_CORE_OUT.2, C_PMIC_DCDC1_IN.2, C_PMIC_DCDC2_IN.2, C_PMIC_DCDC3_IN.2, C_PMIC_DDR_OUT.2, C_PMIC_INT_LDO.2, C_PMIC_IO_OUT.2, C_PMIC_LDO1.2, C_PMIC_LDO2.2, C_PMIC_MPU_OUT.2, C_PMIC_SYS.2, C_PMIC_USB.2, C_PMIC_VINLDO.2, C_POR_BYPASS.2, C_POR_SENSE.2, C_SD_REG_HF.2, C_SD_REG_IN.2, C_SD_REG_OUT.2, C_SD_SOCKET_BULK.2, C_SD_SOCKET_HF.2, C_SRAM_CORE_1.2, C_SRAM_CORE_BULK.2, C_SRAM_MPU_1.2, C_SRAM_MPU_BULK.2, C_USB_ESD.2, C_USB_VBUS_SENSE.2, C_VDDA1P8V_USB0.2, C_VDDA1P8V_USB1.2, C_VDDA3P3V_USB0.2, C_VDDA3P3V_USB1.2, C_VDDS_1.2, C_VDDS_2.2, C_VDDS_3.2, C_VDDS_4.2, C_VDDS_BULK.2, C_VDDS_OSC.2, C_VDDS_PLL_CORE_LCD.2, C_VDDS_PLL_DDR.2, C_VDDS_PLL_MPU.2, C_VDDS_RTC.2, C_VREF_CPU.2, C_VREF_RAM_CA.2, C_VREF_RAM_DQ.2, C_XTAL_IN.2, C_XTAL_OUT.2, D_USB_VBUS_SENSE.2, J_BAT.3, J_LCD.53, J_LCD.54, J_SD.6, J_SD.10, J_SD.11, J_SD.12, J_SD.13, J_SD.14, J_USB.1, J_USB.2, J_USB.3, J_USB.4, J_USB.13, J_USB.14, KEY_A.2, KEY_B.2, KEY_DOWN.2, KEY_LEFT.2, KEY_MENU.2, KEY_RIGHT.2, KEY_SELECT.2, KEY_START.2, KEY_UP.2, KEY_X.2, KEY_Y.2, R_AUDIO_PD.2, R_DDR_VTP.2, R_DDR_ZQ.2, R_IO_BOOST_LO.2, R_LCD_BL_PD.2, R_LCD_BL_SENSE.2, R_LCD_CTRL_PD.2, R_LCD_RESET_PD.2, R_SYSBOOT3.1, R_SYSBOOT5.1, R_SYSBOOT6.1, R_SYSBOOT7.1, R_SYSBOOT8.1, R_SYSBOOT9.1, R_SYSBOOT10.1, R_SYSBOOT11.1, R_SYSBOOT12.1, R_SYSBOOT13.1, R_SYSBOOT15.1, R_TCK.1, R_TRSTn.1, R_USB_CC1.2, R_USB_CC2.2, R_VREF_LO.2, SW_POWER.3, SW_RESET.3, TP_BAT_GND.1, TP_GND.1, TP_UART_GND.1, U_AUDIO.3, U_AUDIO.11, U_AUDIO.15, U_AUDIO.17, U_IO_BOOST.4, U_KEYS.10, U_KEYS.15, U_KEYS.16, U_KEYS.17, U_LCD_BL.4, U_LCD_PWM_BUF.1, U_LCD_PWM_BUF.3, U_PMIC.30, U_PMIC.33, U_PMIC.34, U_PMIC.41, U_PMIC.49, U_POR.2, U_RAM.2, U_RAM.4, U_RAM.5, U_RAM.7, U_RAM.12, U_RAM.14, U_RAM.16, U_RAM.21, U_RAM.25, U_RAM.34, U_RAM.68, U_RAM.69, U_RAM.71, U_RAM.73, U_RAM.81, U_RAM.82, U_RAM.86, U_RAM.87, U_RAM.92, U_RAM.94, U_RAM.96, U_SD_REG.1, U_SD_REG.4, U_SD_REG.5, U_SD_REG.9, U_SOC.1, U_SOC.18, U_SOC.56, U_SOC.73, U_SOC.92, U_SOC.98, U_SOC.99, U_SOC.102, U_SOC.109, U_SOC.110, U_SOC.111, U_SOC.116, U_SOC.117, U_SOC.118, U_SOC.120, U_SOC.121, U_SOC.127, U_SOC.128, U_SOC.129, U_SOC.130, U_SOC.131, U_SOC.132, U_SOC.133, U_SOC.134, U_SOC.135, U_SOC.138, U_SOC.145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
I2C0_SCL: R_PMIC_SCL.2, U_KEYS.12, U_PMIC.28, U_SOC.273
I2C0_SDA: R_PMIC_SDA.2, U_KEYS.13, U_PMIC.27, U_SOC.291
IO_3V3: C_HV2_1.1, C_HV2_2.1, C_HV2_BULK.1, C_HV5_1.1, C_HV5_2.1, C_HV5_BULK.1, C_HV6_1.1, C_HV6_2.1, C_HV6_3.1, C_HV6_4.1, C_HV6_5.1, C_HV6_6.1, C_HV6_BULK.1, C_KEYS_BULK.1, C_KEYS_HF.1, C_LCD_BULK.1, C_LCD_IO_HF.1, C_LCD_VCI_HF.1, C_PMIC_IO_OUT.1, C_VDDA3P3V_USB0.1, C_VDDA3P3V_USB1.1, J_LCD.41, J_LCD.42, R_EMU0.1, R_EMU1.1, R_KEYS_RESET.1, R_LCD_CS_PU.1, R_PMIC_INT.1, R_PMIC_SCL.1, R_PMIC_SDA.1, R_SD_CD.1, R_SYSBOOT0.1, R_SYSBOOT1.1, R_SYSBOOT2.1, R_SYSBOOT4.1, R_SYSBOOT14.1, R_TDI.1, R_TMS.1, R_WARMRSTn.1, TP_IO_3V3.1, TP_UART_IO_3V3.1, U_KEYS.9, U_PMIC.43, U_SD_REG.3, U_SOC.85, U_SOC.86, U_SOC.104, U_SOC.167, U_SOC.176, U_SOC.185, U_SOC.194, U_SOC.203, U_SOC.221, U_SOC.240, U_SOC.241, U_SOC.244, U_SOC.245, U_SOC.265, U_SOC.267
IO_BOOST_FB: C_IO_BOOST_FF.2, R_IO_BOOST_HI.2, R_IO_BOOST_LO.1, U_IO_BOOST.1
IO_BOOST_SW: L_IO_BOOST.2, U_IO_BOOST.5
JTAG_EMU0: R_EMU0.2, TP_JTAG_EMU0.1, U_SOC.237
JTAG_EMU1: R_EMU1.2, TP_JTAG_EMU1.1, U_SOC.236
JTAG_TCK: R_TCK.2, TP_JTAG_TCK.1, U_SOC.199
JTAG_TDI: R_TDI.2, TP_JTAG_TDI.1, U_SOC.182
JTAG_TDO: TP_JTAG_TDO.1, U_SOC.181
JTAG_TMS: R_TMS.2, TP_JTAG_TMS.1, U_SOC.183
JTAG_TRSTn: R_TRSTn.2, TP_JTAG_TRSTn.1, U_SOC.164
KEYS_RESETn: R_KEYS_RESET.2, U_KEYS.18
KEY_A.pin1 to U_KEYS.GPA4: KEY_A.1, U_KEYS.25
KEY_B.pin1 to U_KEYS.GPA5: KEY_B.1, U_KEYS.26
KEY_DOWN.pin1 to U_KEYS.GPA1: KEY_DOWN.1, U_KEYS.22
KEY_LEFT.pin1 to U_KEYS.GPA2: KEY_LEFT.1, U_KEYS.23
KEY_MENU.pin1 to U_KEYS.GPB2: KEY_MENU.1, U_KEYS.3
KEY_RIGHT.pin1 to U_KEYS.GPA3: KEY_RIGHT.1, U_KEYS.24
KEY_SELECT.pin1 to U_KEYS.GPB0: KEY_SELECT.1, U_KEYS.1
KEY_START.pin1 to U_KEYS.GPB1: KEY_START.1, U_KEYS.2
KEY_UP.pin1 to U_KEYS.GPA0: KEY_UP.1, U_KEYS.21
KEY_X.pin1 to U_KEYS.GPA6: KEY_X.1, U_KEYS.27
KEY_Y.pin1 to U_KEYS.GPB3: KEY_Y.1, U_KEYS.4
LCD_BL_COMP: C_LCD_BL_COMP.1, U_LCD_BL.5
LCD_BL_CTRL: R_LCD_CTRL_PD.1, U_LCD_BL.2, U_LCD_PWM_BUF.4
LCD_BL_PWM: R_LCD_BL_PD.1, U_LCD_PWM_BUF.2, U_SOC.251
LCD_BL_SW: D_LCD_BL.2, L_LCD_BL.2, U_LCD_BL.3
LCD_CS1n: J_LCD.9, R_LCD_CS_PU.2, U_SOC.255
LCD_DATA0: R_LCD_DATA0.1, R_SYSBOOT0.2, U_SOC.15
LCD_DATA1: R_LCD_DATA1.1, R_SYSBOOT1.2, U_SOC.33
LCD_DATA2: R_LCD_DATA2.1, R_SYSBOOT2.2, U_SOC.51
LCD_DATA3: R_LCD_DATA3.1, R_SYSBOOT3.2, U_SOC.69
LCD_DATA4: R_LCD_DATA4.1, R_SYSBOOT4.2, U_SOC.16
LCD_DATA5: R_LCD_DATA5.1, R_SYSBOOT5.2, U_SOC.34
LCD_DATA6: R_LCD_DATA6.1, R_SYSBOOT6.2, U_SOC.52
LCD_DATA7: R_LCD_DATA7.1, R_SYSBOOT7.2, U_SOC.70
LCD_DATA8: R_LCD_DATA8.1, R_SYSBOOT8.2, U_SOC.17
LCD_DATA9: R_LCD_DATA9.1, R_SYSBOOT9.2, U_SOC.35
LCD_DATA10: R_LCD_DATA10.1, R_SYSBOOT10.2, U_SOC.53
LCD_DATA11: R_LCD_DATA11.1, R_SYSBOOT11.2, U_SOC.71
LCD_DATA12: R_LCD_DATA12.1, R_SYSBOOT12.2, U_SOC.36
LCD_DATA13: R_LCD_DATA13.1, R_SYSBOOT13.2, U_SOC.54
LCD_DATA14: R_LCD_DATA14.1, R_SYSBOOT14.2, U_SOC.72
LCD_DATA15: R_LCD_DATA15.1, R_SYSBOOT15.2, U_SOC.88
LCD_LED_A: C_LCD_BL_OUT.1, D_LCD_BL.1, J_LCD.3, J_LCD.4
LCD_LED_K: J_LCD.1, J_LCD.2, R_LCD_BL_SENSE.1, U_LCD_BL.6
LCD_RESETn: J_LCD.8, R_LCD_RESET_PD.1, U_SOC.220
LCD_SPI_CLK: J_LCD.10, U_SOC.289
LCD_SPI_MOSI: J_LCD.11, U_SOC.272
LDO2_3V3: C_PMIC_LDO2.1, U_PMIC.1
PERIPH_3V3: C_AUDIO_BULK.1, C_AUDIO_HF.1, C_HV4_1.1, C_HV4_2.1, C_HV4_BULK.1, C_POR_SENSE.1, C_SD_REG_OUT.1, C_SD_SOCKET_BULK.1, C_SD_SOCKET_HF.1, J_SD.4, L_SD_REG.2, R_SD_CMD.1, R_SD_DAT0.1, R_SD_DAT1.1, R_SD_DAT2.1, R_SD_DAT3.1, U_AUDIO.2, U_AUDIO.7, U_AUDIO.8, U_POR.5, U_SD_REG.6, U_SOC.242, U_SOC.243
PERIPH_SW: L_SD_REG.1, U_SD_REG.7
PMIC_BUTTONn: SW_POWER.1, U_PMIC.25
PMIC_BYPASS: C_PMIC_BYPASS.1, U_PMIC.47
PMIC_ENABLE: U_PMIC.9, U_SOC.93
PMIC_INT_LDO: C_PMIC_INT_LDO.1, U_PMIC.48
PMIC_INTn: R_PMIC_INT.2, U_PMIC.45, U_SOC.308
PMIC_MAIN_PGOOD: U_PMIC.26, U_POR.3
PMIC_RESETn: R_PMIC_RESET.2, U_PMIC.44
PMIC_WAKEUPn: R_PMIC_WAKEUP.2, U_PMIC.13, U_SOC.75
RTC_PORn: U_PMIC.46, U_SOC.74
R_LCD_DATA0.pin2 to J_LCD.pin12: J_LCD.12, R_LCD_DATA0.2
R_LCD_DATA1.pin2 to J_LCD.pin13: J_LCD.13, R_LCD_DATA1.2
R_LCD_DATA2.pin2 to J_LCD.pin14: J_LCD.14, R_LCD_DATA2.2
R_LCD_DATA3.pin2 to J_LCD.pin15: J_LCD.15, R_LCD_DATA3.2
R_LCD_DATA4.pin2 to J_LCD.pin16: J_LCD.16, R_LCD_DATA4.2
R_LCD_DATA5.pin2 to J_LCD.pin17: J_LCD.17, R_LCD_DATA5.2
R_LCD_DATA6.pin2 to J_LCD.pin18: J_LCD.18, R_LCD_DATA6.2
R_LCD_DATA7.pin2 to J_LCD.pin19: J_LCD.19, R_LCD_DATA7.2
R_LCD_DATA8.pin2 to J_LCD.pin20: J_LCD.20, R_LCD_DATA8.2
R_LCD_DATA9.pin2 to J_LCD.pin21: J_LCD.21, R_LCD_DATA9.2
R_LCD_DATA10.pin2 to J_LCD.pin22: J_LCD.22, R_LCD_DATA10.2
R_LCD_DATA11.pin2 to J_LCD.pin23: J_LCD.23, R_LCD_DATA11.2
R_LCD_DATA12.pin2 to J_LCD.pin24: J_LCD.24, R_LCD_DATA12.2
R_LCD_DATA13.pin2 to J_LCD.pin25: J_LCD.25, R_LCD_DATA13.2
R_LCD_DATA14.pin2 to J_LCD.pin26: J_LCD.26, R_LCD_DATA14.2
R_LCD_DATA15.pin2 to J_LCD.pin27: J_LCD.27, R_LCD_DATA15.2
R_LCD_DATA16.pin2 to J_LCD.pin28: J_LCD.28, R_LCD_DATA16.2
R_LCD_DATA17.pin2 to J_LCD.pin29: J_LCD.29, R_LCD_DATA17.2
R_LCD_DATA18.pin2 to J_LCD.pin30: J_LCD.30, R_LCD_DATA18.2
R_LCD_DATA19.pin2 to J_LCD.pin31: J_LCD.31, R_LCD_DATA19.2
R_LCD_DATA20.pin2 to J_LCD.pin32: J_LCD.32, R_LCD_DATA20.2
R_LCD_DATA21.pin2 to J_LCD.pin33: J_LCD.33, R_LCD_DATA21.2
R_LCD_DATA22.pin2 to J_LCD.pin34: J_LCD.34, R_LCD_DATA22.2
R_LCD_DATA23.pin2 to J_LCD.pin35: J_LCD.35, R_LCD_DATA23.2
R_LCD_DE.pin2 to J_LCD.pin52: J_LCD.52, R_LCD_DE.2
R_LCD_HSYNC.pin2 to J_LCD.pin36: J_LCD.36, R_LCD_HSYNC.2
R_LCD_PCLK.pin2 to J_LCD.pin38: J_LCD.38, R_LCD_PCLK.2
R_LCD_VSYNC.pin2 to J_LCD.pin37: J_LCD.37, R_LCD_VSYNC.2
SD_CD: J_SD.9, R_SD_CD.2, U_SOC.309
SD_CLK_CARD: J_SD.5, R_SD_CLK.2
SD_CLK_CPU: R_SD_CLK.1, U_SOC.295
SD_CMD: J_SD.3, R_SD_CMD.2, U_SOC.313
SD_DAT0: J_SD.7, R_SD_DAT0.2, U_SOC.277
SD_DAT1: J_SD.8, R_SD_DAT1.2, U_SOC.259
SD_DAT2: J_SD.1, R_SD_DAT2.2, U_SOC.312
SD_DAT3: J_SD.2, R_SD_DAT3.2, U_SOC.294
SPK_N: J_SPK.2, TP_SPK_N.1, U_AUDIO.10
SPK_P: J_SPK.1, TP_SPK_P.1, U_AUDIO.9
SW_CORE: L_CORE.1, U_PMIC.31
SW_DDR: L_DDR.1, U_PMIC.20
SW_MPU: L_MPU.1, U_PMIC.23
UART0_RX: TP_UART_UART0_RX.1, U_SOC.257
UART0_TX: TP_UART_UART0_TX.1, U_SOC.275
USB0_DM: J_USB.7, J_USB.9, U_SOC.319, U_USB_ESD.1, U_USB_ESD.6
USB0_DP: J_USB.8, J_USB.10, U_SOC.301, U_USB_ESD.3, U_USB_ESD.4
USB0_VBUS_SENSE: C_USB_VBUS_SENSE.1, D_USB_VBUS_SENSE.1, R_USB_VBUS_SENSE.2, U_SOC.266
USB_5V: C_PMIC_USB.1, C_USB_ESD.1, J_USB.15, J_USB.16, R_USB_VBUS_SENSE.1, TP_USB_INPUT.1, U_PMIC.12, U_USB_ESD.5
USB_CC1: J_USB.6, R_USB_CC1.1
USB_CC2: J_USB.12, R_USB_CC2.1
U_SOC.pin2 to U_RAM.pin30: U_RAM.30, U_SOC.2
U_SOC.pin3 to U_RAM.pin47: U_RAM.47, U_SOC.3
U_SOC.pin4 to U_RAM.pin58: U_RAM.58, U_SOC.4
U_SOC.pin5 to U_RAM.pin77: U_RAM.77, U_SOC.5
U_SOC.pin6 to U_RAM.pin42: U_RAM.42, U_SOC.6
U_SOC.pin7 to U_RAM.pin10: U_RAM.10, U_SOC.7
U_SOC.pin8 to U_RAM.pin62: U_RAM.62, U_SOC.8
U_SOC.pin9 to U_RAM.pin67: U_RAM.67, U_SOC.9
U_SOC.pin10 to U_RAM.pin49: U_RAM.49, U_SOC.10
U_SOC.pin11 to U_RAM.pin51: U_RAM.51, U_SOC.11
U_SOC.pin12 to U_RAM.pin66: U_RAM.66, U_SOC.12
U_SOC.pin13 to U_RAM.pin37: U_RAM.37, U_SOC.13
U_SOC.pin14 to U_RAM.pin38: U_RAM.38, U_SOC.14
U_SOC.pin20 to U_RAM.pin43: U_RAM.43, U_SOC.20
U_SOC.pin21 to U_RAM.pin78: U_RAM.78, U_SOC.21
U_SOC.pin22 to U_RAM.pin57: U_RAM.57, U_SOC.22
U_SOC.pin23 to U_RAM.pin31: U_RAM.31, U_SOC.23
U_SOC.pin24 to U_RAM.pin63: U_RAM.63, U_SOC.24
U_SOC.pin25 to U_RAM.pin32: U_RAM.32, U_SOC.25
U_SOC.pin26 to U_RAM.pin27: U_RAM.27, U_SOC.26
U_SOC.pin27 to U_RAM.pin36: U_RAM.36, U_SOC.27
U_SOC.pin28 to U_RAM.pin35: U_RAM.35, U_SOC.28
U_SOC.pin29 to U_RAM.pin50: U_RAM.50, U_SOC.29
U_SOC.pin30 to U_RAM.pin53: U_RAM.53, U_SOC.30
U_SOC.pin31 to U_RAM.pin40: U_RAM.40, U_SOC.31
U_SOC.pin32 to U_RAM.pin39: U_RAM.39, U_SOC.32
U_SOC.pin38 to U_RAM.pin44: U_RAM.44, U_SOC.38
U_SOC.pin39 to U_RAM.pin29: U_RAM.29, U_SOC.39
U_SOC.pin41 to U_RAM.pin61: U_RAM.61, U_SOC.41
U_SOC.pin42 to U_RAM.pin45: U_RAM.45, U_SOC.42
U_SOC.pin43 to U_RAM.pin90: U_RAM.90, U_SOC.43
U_SOC.pin44 to U_RAM.pin48: U_RAM.48, U_SOC.44
U_SOC.pin46 to U_RAM.pin17: U_RAM.17, U_SOC.46
U_SOC.pin47 to U_RAM.pin19: U_RAM.19, U_SOC.47
U_SOC.pin48 to U_RAM.pin22: U_RAM.22, U_SOC.48
U_SOC.pin49 to U_RAM.pin54: U_RAM.54, U_SOC.49
U_SOC.pin50 to U_RAM.pin70: U_RAM.70, U_SOC.50
U_SOC.pin57 to U_RAM.pin28: U_RAM.28, U_SOC.57
U_SOC.pin58 to U_RAM.pin80: U_RAM.80, U_SOC.58
U_SOC.pin59 to U_RAM.pin46: U_RAM.46, U_SOC.59
U_SOC.pin60 to U_RAM.pin59: U_RAM.59, U_SOC.60
U_SOC.pin61 to U_RAM.pin41: U_RAM.41, U_SOC.61
U_SOC.pin62 to U_RAM.pin64: U_RAM.64, U_SOC.62
U_SOC.pin64 to U_RAM.pin52: U_RAM.52, U_SOC.64
U_SOC.pin65 to U_RAM.pin33: U_RAM.33, U_SOC.65
U_SOC.pin66 to U_RAM.pin72: U_RAM.72, U_SOC.66
U_SOC.pin67 to U_RAM.pin23: U_RAM.23, U_SOC.67
U_SOC.pin68 to U_RAM.pin56: U_RAM.56, U_SOC.68
U_SOC.pin76 to U_RAM.pin79: U_RAM.79, U_SOC.76
U_SOC.pin87 to R_LCD_HSYNC.pin1: R_LCD_HSYNC.1, U_SOC.87
U_SOC.pin89 to R_LCD_VSYNC.pin1: R_LCD_VSYNC.1, U_SOC.89
U_SOC.pin90 to R_LCD_PCLK.pin1: R_LCD_PCLK.1, U_SOC.90
U_SOC.pin105 to R_LCD_DE.pin1: R_LCD_DE.1, U_SOC.105
U_SOC.pin178 to R_LCD_DATA22.pin1: R_LCD_DATA22.1, U_SOC.178
U_SOC.pin179 to R_LCD_DATA23.pin1: R_LCD_DATA23.1, U_SOC.179
U_SOC.pin196 to R_LCD_DATA21.pin1: R_LCD_DATA21.1, U_SOC.196
U_SOC.pin213 to R_LCD_DATA18.pin1: R_LCD_DATA18.1, U_SOC.213
U_SOC.pin214 to R_LCD_DATA19.pin1: R_LCD_DATA19.1, U_SOC.214
U_SOC.pin215 to R_LCD_DATA20.pin1: R_LCD_DATA20.1, U_SOC.215
U_SOC.pin233 to R_LCD_DATA16.pin1: R_LCD_DATA16.1, U_SOC.233
U_SOC.pin234 to R_LCD_DATA17.pin1: R_LCD_DATA17.1, U_SOC.234
VBAT: C_BATTERY.1, J_BAT.1, TP_BAT_INPUT.1, U_PMIC.4, U_PMIC.5, U_PMIC.6
VDDS_1V8: C_PMIC_LDO1.1, C_POR_BYPASS.1, C_VDDS_1.1, C_VDDS_2.1, C_VDDS_3.1, C_VDDS_4.1, C_VDDS_BULK.1, C_VDDS_RTC.1, R_CPU_POR.1, R_PMIC_RESET.1, R_PMIC_WAKEUP.1, U_PMIC.3, U_PMIC.18, U_POR.6, U_SOC.95, U_SOC.103, U_SOC.112, U_SOC.150, U_SOC.158, U_SOC.226, U_SOC.239, U_SOC.248
VDD_CORE: C_CORE_1.1, C_CORE_2.1, C_CORE_3.1, C_CORE_4.1, C_CORE_5.1, C_CORE_6.1, C_CORE_7.1, C_CORE_8.1, C_CORE_BULK.1, C_PMIC_CORE_OUT.1, L_CORE.2, U_PMIC.29, U_SOC.96, U_SOC.97, U_SOC.100, U_SOC.101, U_SOC.114, U_SOC.115, U_SOC.119, U_SOC.136, U_SOC.137, U_SOC.139, U_SOC.155, U_SOC.157, U_SOC.169, U_SOC.188, U_SOC.192, U_SOC.207, U_SOC.208, U_SOC.211, U_SOC.228, U_SOC.229
VDD_MPU: C_MPU_1.1, C_MPU_2.1, C_MPU_3.1, C_MPU_4.1, C_MPU_5.1, C_MPU_BULK.1, C_PMIC_MPU_OUT.1, L_MPU.2, U_PMIC.24, U_SOC.19, U_SOC.168, U_SOC.186, U_SOC.204, U_SOC.222, U_SOC.223, U_SOC.224, U_SOC.225
VIO_BOOST5V: C_IO_BOOST_FF.1, C_IO_BOOST_OUT1.1, C_IO_BOOST_OUT2.1, C_LCD_BL_IN.1, C_PMIC_VINLDO.1, C_SD_REG_HF.1, C_SD_REG_IN.1, L_LCD_BL.1, R_IO_BOOST_HI.1, U_IO_BOOST.6, U_LCD_BL.1, U_PMIC.2, U_PMIC.42, U_SD_REG.2
VSYS: C_IO_BOOST_IN.1, C_PMIC_DCDC1_IN.1, C_PMIC_DCDC2_IN.1, C_PMIC_DCDC3_IN.1, C_PMIC_SYS.1, L_IO_BOOST.1, U_IO_BOOST.2, U_IO_BOOST.3, U_PMIC.7, U_PMIC.8, U_PMIC.21, U_PMIC.22, U_PMIC.32, U_PMIC.39
WARM_RESETn: R_WARMRSTn.2, SW_RESET.1, TP_WARM_RESETn.1, U_SOC.163
XTAL_DRIVE: C_XTAL_OUT.1, R_XTAL_DAMP.2, X_MAIN.3
XTAL_IN: C_XTAL_IN.1, R_XTAL_BIAS_DNP.1, U_SOC.180, X_MAIN.1
XTAL_OUT: R_XTAL_BIAS_DNP.2, R_XTAL_DAMP.1, U_SOC.197
